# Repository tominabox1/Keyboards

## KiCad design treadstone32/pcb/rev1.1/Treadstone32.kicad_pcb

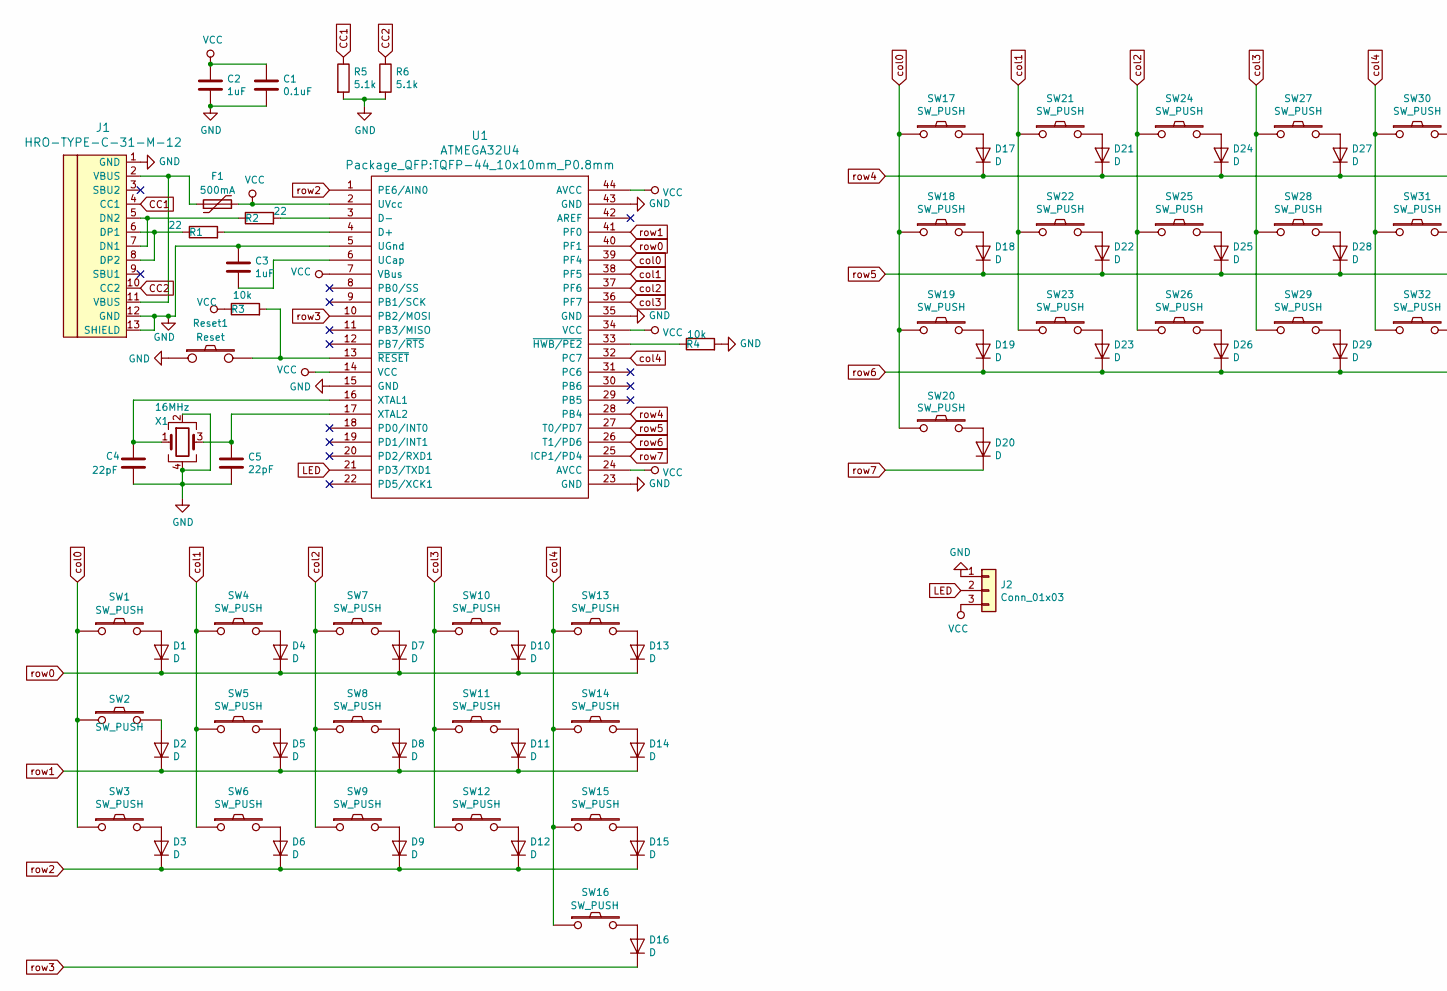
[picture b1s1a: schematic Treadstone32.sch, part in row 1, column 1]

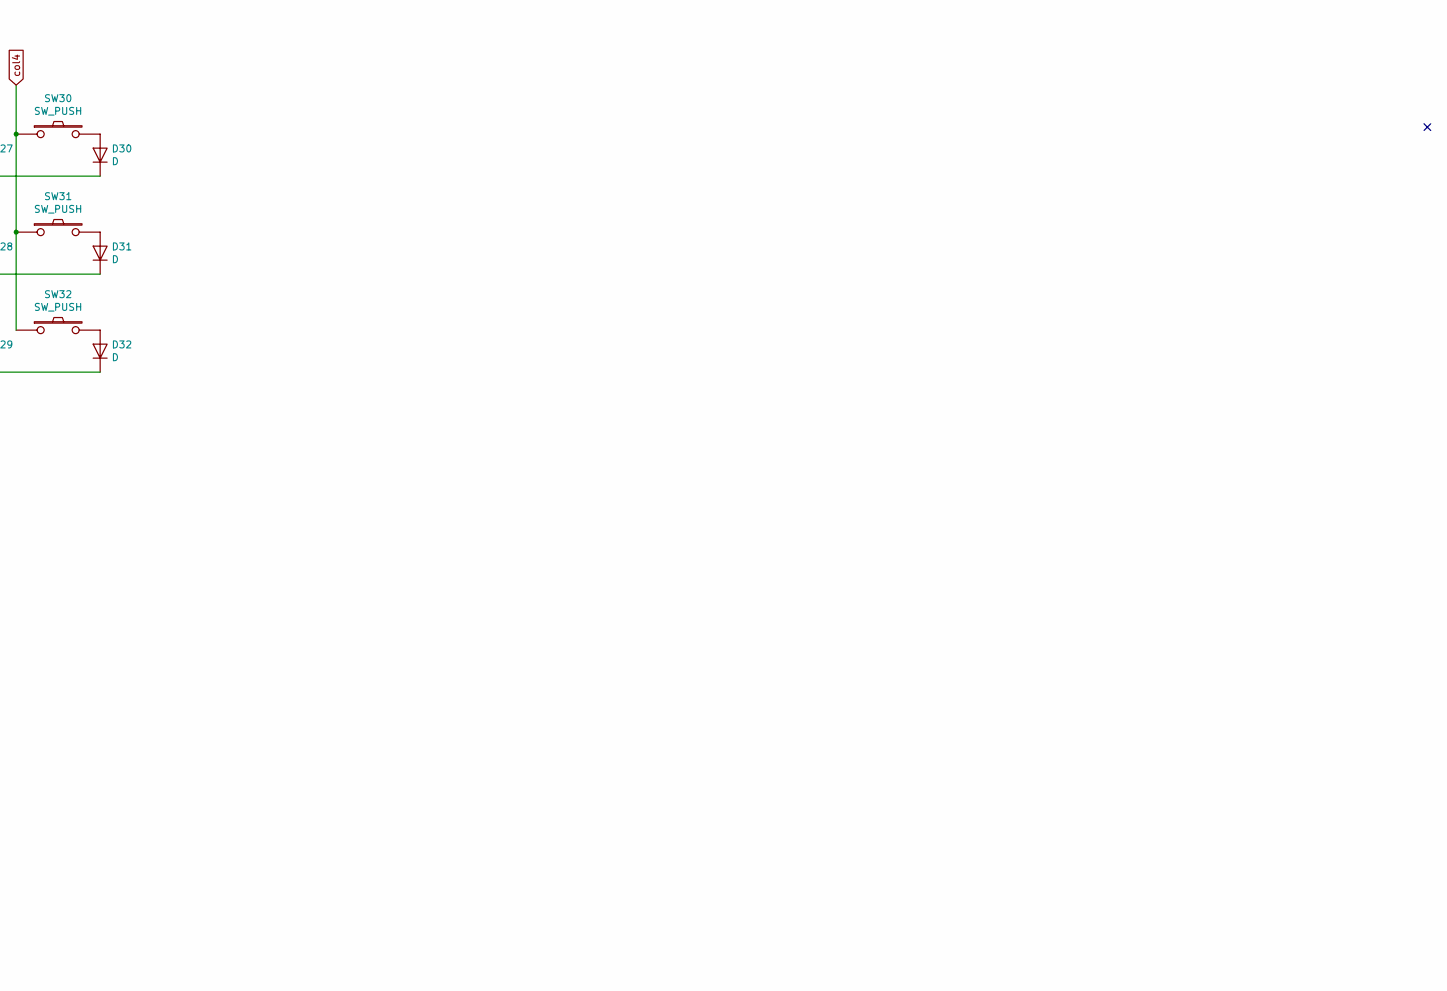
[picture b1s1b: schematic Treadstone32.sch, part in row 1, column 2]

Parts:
C1: 0.1uF; C_1206_3216Metric_Pad1.42x1.75mm_HandSolder
C2, C3: 1uF; C_1206_3216Metric_Pad1.42x1.75mm_HandSolder
C4, C5: 22pF; C_1206_3216Metric_Pad1.42x1.75mm_HandSolder
D1, D2, D3, D4, D5, D6, D7, D8, D9, D10, D11, D12, D13, D14, D15, D16, D17, D18, D19, D20, D21, D22, D23, D24, D25, D26, D27, D28, D29, D30, D31, D32: D; D3_SMD_only_front
F1: 500mA; Fuse_0805_2012Metric_Pad1.15x1.40mm_HandSolder
J1: HRO-TYPE-C-31-M-12; HRO-TYPE-C-31-M-12-HandSoldering
J2: Conn_01x03; StripLED_front
R1, R2: 22; R_1206_3216Metric_Pad1.42x1.75mm_HandSolder
R3, R4: 10k; R_1206_3216Metric_Pad1.42x1.75mm_HandSolder
R5, R6: 5.1k; R_1206_3216Metric_Pad1.42x1.75mm_HandSolder
Reset1: Reset; SW_SPST_PTS810
SW1, SW2, SW3, SW4, SW5, SW6, SW7, SW8, SW9, SW10, SW11, SW12, SW13, SW14, SW15, SW16, SW17, SW18, SW19, SW20, SW21, SW22, SW23, SW24, SW25, SW26, SW27, SW28, SW29, SW30, SW31, SW32: SW_PUSH; CherryMX_Hotswap_front
U1: ATMEGA32U4; TQFP-44_10x10mm_P0.8mm
X1: 16MHz; Crystal_SMD_3225-4Pin_3.2x2.5mm_HandSoldering

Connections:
CC1: J1.4 (CC1), R5.1
CC2: J1.10 (CC2), R6.1
GND: C1.2, C2.2, C3.1, C4.2, C5.2, J1.1 (GND), J1.12 (GND), J1.13 (SHIELD), J2.1, R4.2, R5.2, R6.2, Reset1.1, U1.5 (UGnd), U1.15 (GND), U1.23 (GND), U1.35 (GND), U1.43 (GND), X1.2, X1.4
LED: J2.2, U1.21 (PD3/TXD1)
unnamed: C3.2, U1.6 (UCap)
unnamed: C4.1, U1.16 (XTAL1), X1.1
unnamed: C5.1, U1.17 (XTAL2), X1.3
unnamed: D1.2 (A), SW1.2
unnamed: D2.2 (A), SW2.2
unnamed: D3.2 (A), SW3.2
unnamed: D4.2 (A), SW4.2
unnamed: D5.2 (A), SW5.2
unnamed: D6.2 (A), SW6.2
unnamed: D7.2 (A), SW7.2
unnamed: D8.2 (A), SW8.2
unnamed: D9.2 (A), SW9.2
unnamed: D10.2 (A), SW10.2
unnamed: D11.2 (A), SW11.2
unnamed: D12.2 (A), SW12.2
unnamed: D13.2 (A), SW13.2
unnamed: D14.2 (A), SW14.2
unnamed: D15.2 (A), SW15.2
unnamed: D16.2 (A), SW16.2
unnamed: D17.2 (A), SW17.2
unnamed: D18.2 (A), SW18.2
unnamed: D19.2 (A), SW19.2
unnamed: D20.2 (A), SW20.2
unnamed: D21.2 (A), SW21.2
unnamed: D22.2 (A), SW22.2
unnamed: D23.2 (A), SW23.2
unnamed: D24.2 (A), SW24.2
unnamed: D25.2 (A), SW25.2
unnamed: D26.2 (A), SW26.2
unnamed: D27.2 (A), SW27.2
unnamed: D28.2 (A), SW28.2
unnamed: D29.2 (A), SW29.2
unnamed: D30.2 (A), SW30.2
unnamed: D31.2 (A), SW31.2
unnamed: D32.2 (A), SW32.2
unnamed: F1.1, J1.2 (VBUS), J1.11 (VBUS)
unnamed: J1.5 (DN2), J1.7 (DN1), R2.1
unnamed: J1.6 (DP1), J1.8 (DP2), R1.1
unnamed: R1.2, U1.4 (D+)
unnamed: R2.2, U1.3 (D-)
unnamed: R3.2, Reset1.2, U1.13 (~RESET)
unnamed: R4.1, U1.33 (~HWB/PE2)
VCC: C1.1, C2.1, F1.2, J2.3, R3.1, U1.2 (UVcc), U1.7 (VBus), U1.14 (VCC), U1.24 (AVCC), U1.34 (VCC), U1.44 (AVCC)
col0: SW1.1, SW2.1, SW3.1, SW17.1, SW18.1, SW19.1, SW20.1, U1.39 (PF4)
col1: SW4.1, SW5.1, SW6.1, SW21.1, SW22.1, SW23.1, U1.38 (PF5)
col2: SW7.1, SW8.1, SW9.1, SW24.1, SW25.1, SW26.1, U1.37 (PF6)
col3: SW10.1, SW11.1, SW12.1, SW27.1, SW28.1, SW29.1, U1.36 (PF7)
col4: SW13.1, SW14.1, SW15.1, SW16.1, SW30.1, SW31.1, SW32.1, U1.32 (PC7)
row0: D1.1 (K), D4.1 (K), D7.1 (K), D10.1 (K), D13.1 (K), U1.40 (PF1)
row1: D2.1 (K), D5.1 (K), D8.1 (K), D11.1 (K), D14.1 (K), U1.41 (PF0)
row2: D3.1 (K), D6.1 (K), D9.1 (K), D12.1 (K), D15.1 (K), U1.1 (PE6/AIN0)
row3: D16.1 (K), U1.10 (PB2/MOSI)
row4: D17.1 (K), D21.1 (K), D24.1 (K), D27.1 (K), D30.1 (K), U1.28 (PB4)
row5: D18.1 (K), D22.1 (K), D25.1 (K), D28.1 (K), D31.1 (K), U1.27 (T0/PD7)
row6: D19.1 (K), D23.1 (K), D26.1 (K), D29.1 (K), D32.1 (K), U1.26 (T1/PD6)
row7: D20.1 (K), U1.25 (ICP1/PD4)

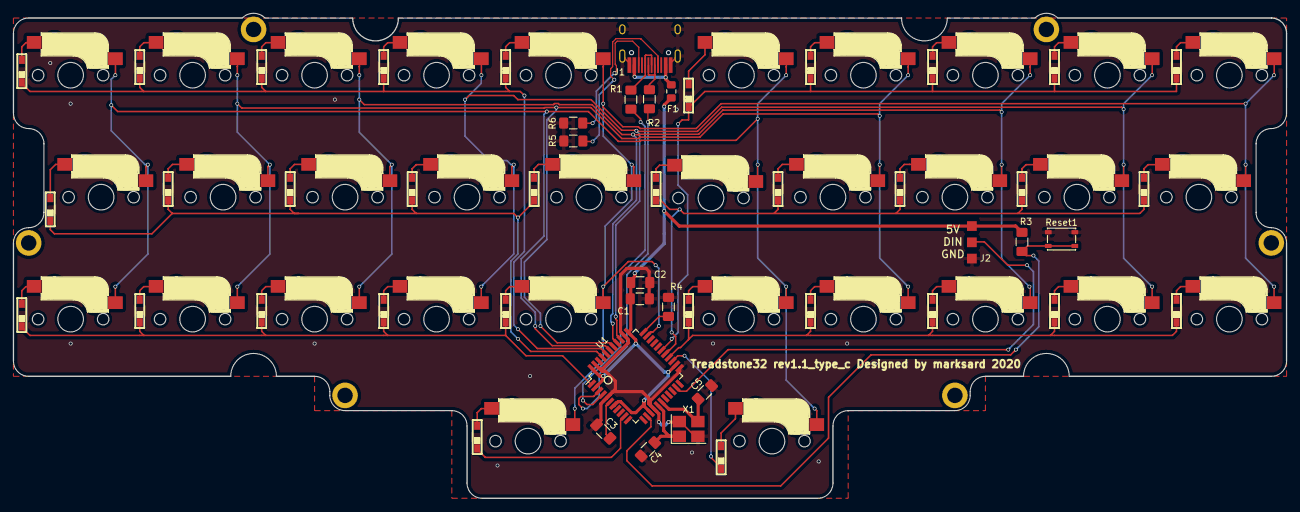
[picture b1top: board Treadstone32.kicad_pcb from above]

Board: 2 copper layers, 198.8 x 75.7 mm, 81 parts (0 on the bottom side), 60 nets.

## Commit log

2020-02-29 Convert PCB to support USB type C connector
    Added HRO Type C to replace J1 on schematic as well as C to C identifying resistors. Modified board edge cut and USB connector, re-routed data lines to new connector. Fixed issues with non-connecting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
2020-02-29 Add no-connects to unused USB pins
    Add no-connects to unused USB pins
